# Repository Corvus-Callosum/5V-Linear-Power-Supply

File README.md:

# Power-Supply

## Schematic:

## 3D View

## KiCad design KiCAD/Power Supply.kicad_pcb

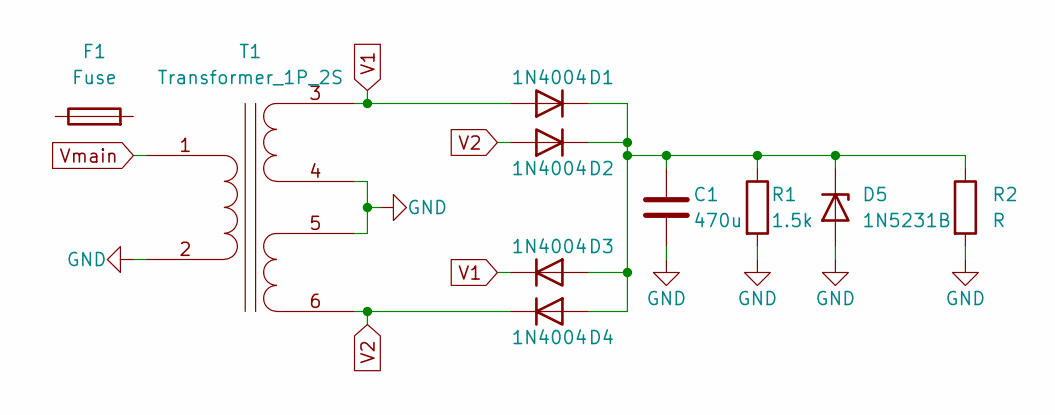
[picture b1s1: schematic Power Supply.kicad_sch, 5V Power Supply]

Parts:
C1: 470u; CP_Radial_D7.5mm_P2.50mm
D1, D2, D3, D4: 1N4004; D_DO-41_SOD81_P7.62mm_Horizontal
D5: 1N5231B; D_DO-41_SOD81_P7.62mm_Horizontal
F1: Fuse; Fuseholder_Cylinder-5x20mm_Schurter_0031_8201_Horizontal_Op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
R1: 1.5k; R_Axial_DIN0411_L9.9mm_D3.6mm_P12.70mm_Horizontal
R2: R; R_Axial_DIN0411_L9.9mm_D3.6mm_P12.70mm_Horizontal
T1: Transformer_1P_2S; XFMR_PC-34-125

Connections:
GND: C1.2, D5.2 (A), R1.2, R2.2, T1.2 (AB), T1.4 (SB), T1.5 (SC)
unnamed: C1.1, D1.1 (K), D2.1 (K), D3.2 (A), D4.2 (A), D5.1 (K), R1.1, R2.1
V1: D1.2 (A), D3.1 (K), T1.3 (SA)
V2: D2.2 (A), D4.1 (K), T1.6 (SD)
Vmain: T1.1 (AA)

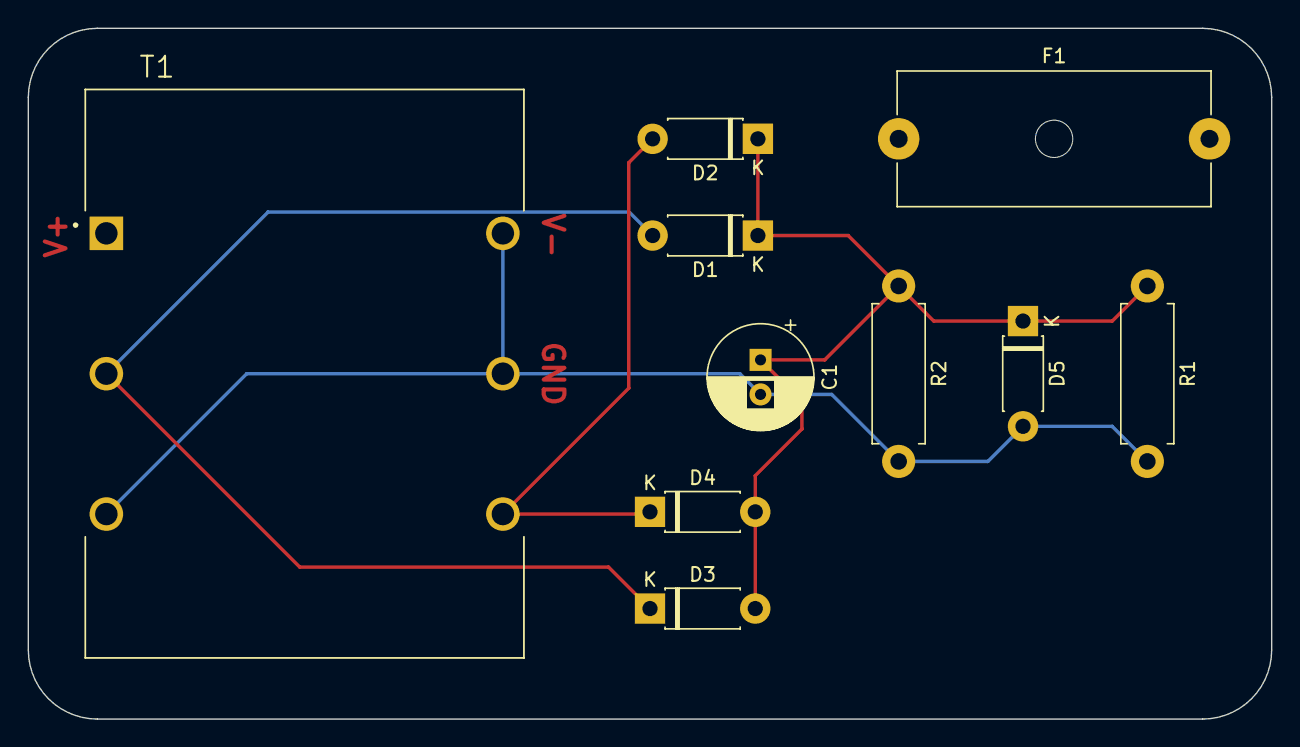
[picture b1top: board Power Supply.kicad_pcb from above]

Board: 2 copper layers, 90.0 x 50.0 mm, 10 parts (0 on the bottom side), 4 nets.
